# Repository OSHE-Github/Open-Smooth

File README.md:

# Open-Smooth
echo "# OPENSmooth" >> README.md
# Project Overview
OPENSmooth introduces an open-source 3D print post-processor that uses acetone vapor and heat to smooth filament layer lines. The system integrates electronic monitors to regulate exposure time and ensure safe operation, reducing risks associated with manual methods. By combining automated vapor control with real-time safety monitoring, the design provides a low-cost, accessible solution to improve the surface quality of 3D-printed parts.
# Bill of Materials

### Physical Construction
| Category | Item | Part Number | Source | Cost |
|----------|------|------------|--------|------|
| Physical Construction | PETG filament | - | Amazon | $15 (per spool) |
| Physical Construction | Enclosure bin | - | Amazon | $12 |
| Physical Construction | Plastic bottles | - | Amazon | $7 |
| Physical Construction | Fan grill | - | Amazon | $5 |
| Physical Construction | Epoxy | - | Amazon | $8 |

### Electronics
| Category | Item | Part Number | Source | Cost |
|----------|------|------------|--------|------|
| Electronics | Heater | - | Amazon | $35 |
| Electronics | Atomizers | - | Amazon | $23 |
| Electronics | Fans (x2) | - | Amazon | $18 |
| Electronics | E-stop | - | Amazon | $12 |
| Electronics | Touchscreen | - | Amazon | $16 |
| Electronics | Servo | - | Amazon | $19 |
| Electronics | IEC plug | - | Amazon | $8 |
| Electronics | IEC cable | - | Amazon | $6 |
| Electronics | RGB lights | - | Amazon | $13 |

### Circuitry
| Category | Item | Part Number | Source | Cost |
|----------|------|------------|--------|------|
| Circuitry | PCB | - | - | $10 |
| Circuitry | Arduino Mega | - | - | $30 |
| Circuitry | ATMEGA328 (x2) | - | DigiKey | $6 |
| Circuitry | Relays (x2) | - | Amazon | $14 |
| Circuitry | Buck converters | - | Amazon | $8 |
| Circuitry | 2N2222A Transistors (x20) | - | DigiKey | $1 |
| Circuitry | Thermistor | - | - | $8 |
| Circuitry | Acetone sensor | - | - | $8 |
| Circuitry | 12V power supply | - | Amazon | $10 |

### Consumables
| Category | Item | Part Number | Source | Cost |
|----------|------|------------|--------|------|
| Consumables | Acetone | - | Amazon | $10 |
| Consumables | Carbon pellets | - | Amazon | $12 |

---

## Tools Used

### Testing and Planning
| Category | Item | Part Number | Source | Cost |
|----------|------|------------|--------|------|
| Testing and Planning | Breadboard | ZYJ-102 | Adafruit | $5.95 |
| Testing and Planning | Multimeter | Fluke 179 | Fluke | $479.99 |
| Testing and Planning | Oscilloscope | MSO6012A | Test Equity | $2955.00 |

### Assembly
| Category | Item | Part Number | Source | Cost |
|----------|------|------------|--------|------|
| Assembly | Solder Iron | FX-888D | Hakko | $121.47 |
| Assembly | Dremel | - | Milwaukee | - |
| Assembly | Drill | - | Milwaukee | - |

### Programming
| Category | Item | Part Number | Source | Cost |
|----------|------|------------|--------|------|
| Programming | Arduino IDE | Arduino IDE 2.3.2 | Arduino | $0 |

# Assembly Overview
### 1. Print All Components
- 3D print all required parts using PETG filament
- Base components (13 parts)
- Filter components (9 parts)
- Rotating table components (4 parts) + servo housing (1 part)
- Recommended to have ~2kg of filament available
- Use supports only where necessary (mainly the table)

### 2. Assemble the Base
- Fit all base components together using the dovetail joints
- Ensure correct orientation (parts only fit one way)
- Press-fit assembly should hold the structure together
- Apply epoxy if additional strength is needed

### 3. Prepare and Assemble the Lid
- Cut and drill openings for:
  - Heater (rear-center)
  - Filter (top-center)
- Mount heater:
  - Cut a circular hole for the heater body
  - Drill mounting holes
  - Install the gasket and secure the heater
- Mount filter:
  - Cut a square intake hole
  - Drill mounting holes (M3)
- Install a limit switch at the bottom edge of the lid to detect the open/closed state

### 4. Assemble and Install the Filter
- Assemble the main filter housing using M3 screws
- Install a 60 mm fan and secure it with M4 screws
- Prepare pellet drawer:
  - Epoxy if printed in two parts
  - Fill with carbon pellets
- Insert pellet drawer and secure with clips and screws
- Cut mounting holes and vent in enclosure
- Attach filter and gasket to enclosure

### 5. Install the Rotating Table System
- Mount the servo into the servo housing
- Route wires through housing cutouts
- Install housing into base (center cutout)
- Attach the spur gear to the servo shaft
- Install the table spacer and the rotating table
- Snap the fan grille into place

### 6. Assemble Atomizers
- Assemble each atomizer:
  - Insert wick into atomizer
  - Secure wick using trimmed nail or pin
- Extend wiring to reach the control PCB
- Repeat for all atomizers
- Fill with acetone and place into holders

### 7. Final Assembly & Integration
- Ensure all mechanical components are secured
- Verify moving parts (table rotation, fan clearance)
- Confirm proper placement of heater, filter, and sensors
- Connect electronics (fans, heater, atomizers, sensors, etc.)
- Perform a system check before operation

### 8. Final Checks
- Verify all fasteners are tight
- Ensure no air leaks around the filter and heater
- Confirm limit switch functionality
- Test electrical connections safely

**Note:**  
Epoxy is optional in most areas but recommended for long-term durability.

# Future Improvements
### Enclosure Stability and Sealing Capability
The enclosure currently uses duct tape to keep a seal with the lid. This works well, but it could be improved. Adding a lid locking mechanism with a layered rubber seal at the base would prevent the lid from unintentionally opening as well as provide a better seal.

### Atomizer bottles
The atomizer bottles we used for this project are made of PET plastic. PET plastic is susceptible to acetone over long periods of time, causing the bottles to likely leak. In our testing, the bottles showed minimal wear, but this doesn't mean they are 100% safe. Bottles made of PP or HDPE plastic would be much better suited for this application.

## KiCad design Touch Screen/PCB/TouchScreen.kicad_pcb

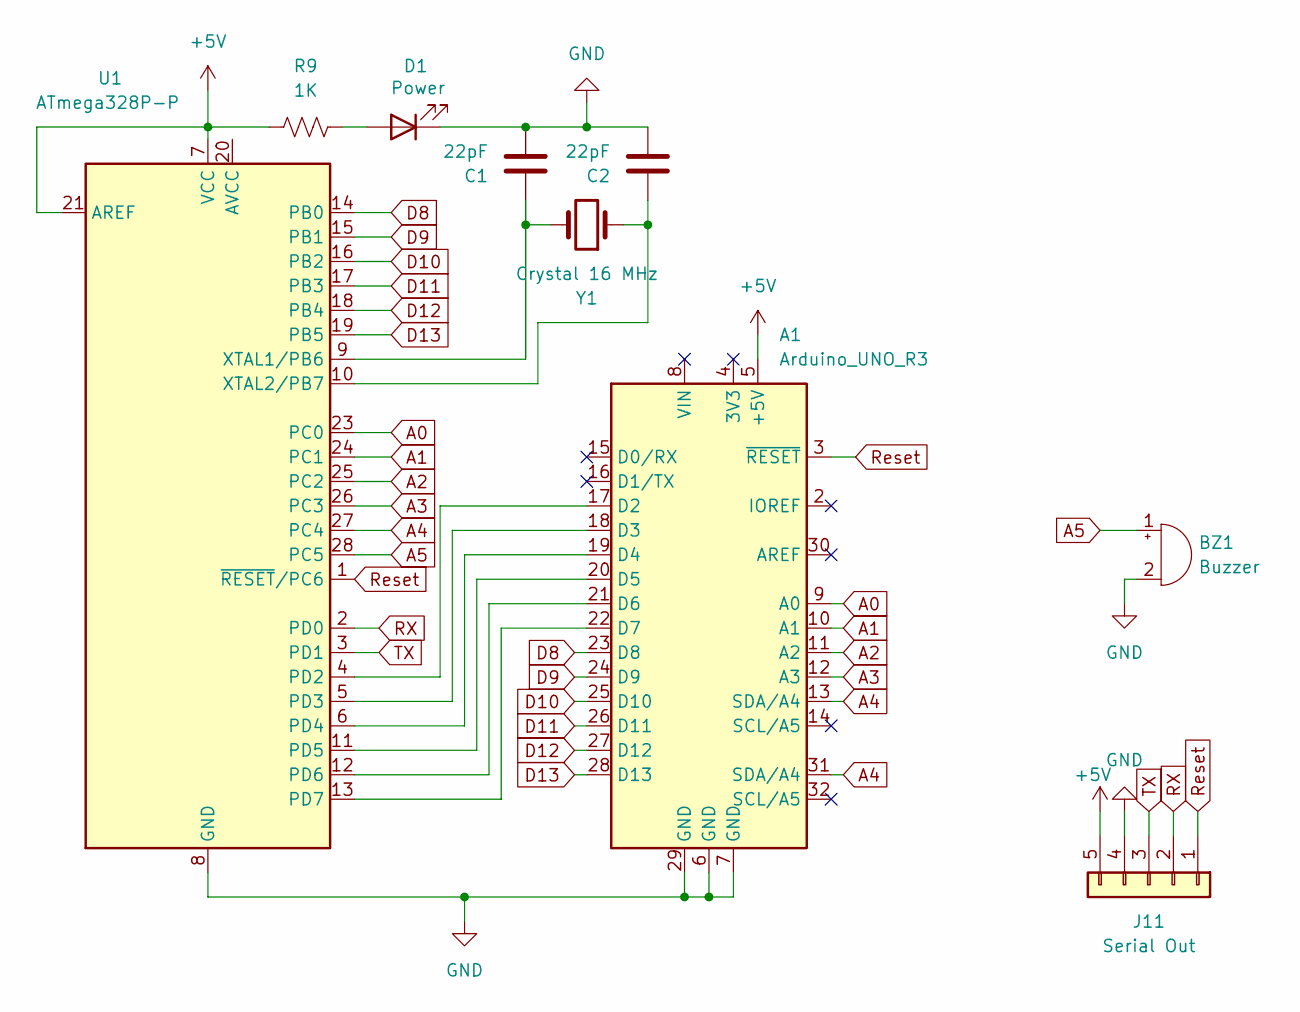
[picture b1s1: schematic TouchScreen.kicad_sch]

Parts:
A1: Arduino_UNO_R3
BZ1: Buzzer; Buzzer_12x9.5RM7.6
C1, C2: 22pF; C_Disc_D3.0mm_W1.6mm_P2.50mm
D1: Power; LED_D5.0mm
J11: Serial Out; JST_XH_B5B-XH-A_1x05_P2.50mm_Vertical
R9: 1K; R_Axial_DIN0309_L9.0mm_D3.2mm_P12.70mm_Horizontal
U1: ATmega328P-P; DIP-28_W7.62mm
Y1: Crystal 16 MHz; Crystal_HC49-4H_Vertical

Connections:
+5V: A1.5 (+5V), J11.5, R9.2, U1.7 (VCC), U1.21 (AREF)
A0: A1.9 (A0), U1.23 (PC0)
A1: A1.10 (A1), U1.24 (PC1)
A2: A1.11 (A2), U1.25 (PC2)
A3: A1.12 (A3), U1.26 (PC3)
A4: A1.13 (SDA/A4), A1.31 (SDA/A4), U1.27 (PC4)
A5: BZ1.1 (+), U1.28 (PC5)
D8: A1.23 (D8), U1.14 (PB0)
D9: A1.24 (D9), U1.15 (PB1)
D10: A1.25 (D10), U1.16 (PB2)
D11: A1.26 (D11), U1.17 (PB3)
D12: A1.27 (D12), U1.18 (PB4)
D13: A1.28 (D13), U1.19 (PB5)
GND: A1.6 (GND), A1.7 (GND), A1.29 (GND), BZ1.2 (-), C1.2, C2.2, D1.1 (K), J11.4, U1.8 (GND), U1.22 (GND)
unnamed: A1.17 (D2), U1.4 (PD2)
unnamed: A1.18 (D3), U1.5 (PD3)
unnamed: A1.19 (D4), U1.6 (PD4)
unnamed: A1.20 (D5), U1.11 (PD5)
unnamed: A1.21 (D6), U1.12 (PD6)
unnamed: A1.22 (D7), U1.13 (PD7)
unnamed: D1.2 (A), R9.1
unnamed: C1.1, U1.9 (XTAL1/PB6), Y1.2
unnamed: C2.1, U1.10 (XTAL2/PB7), Y1.1
RX: J11.2, U1.2 (PD0)
Reset: A1.3 (~RESET), J11.1, U1.1 (~RESET/PC6)
TX: J11.3, U1.3 (PD1)

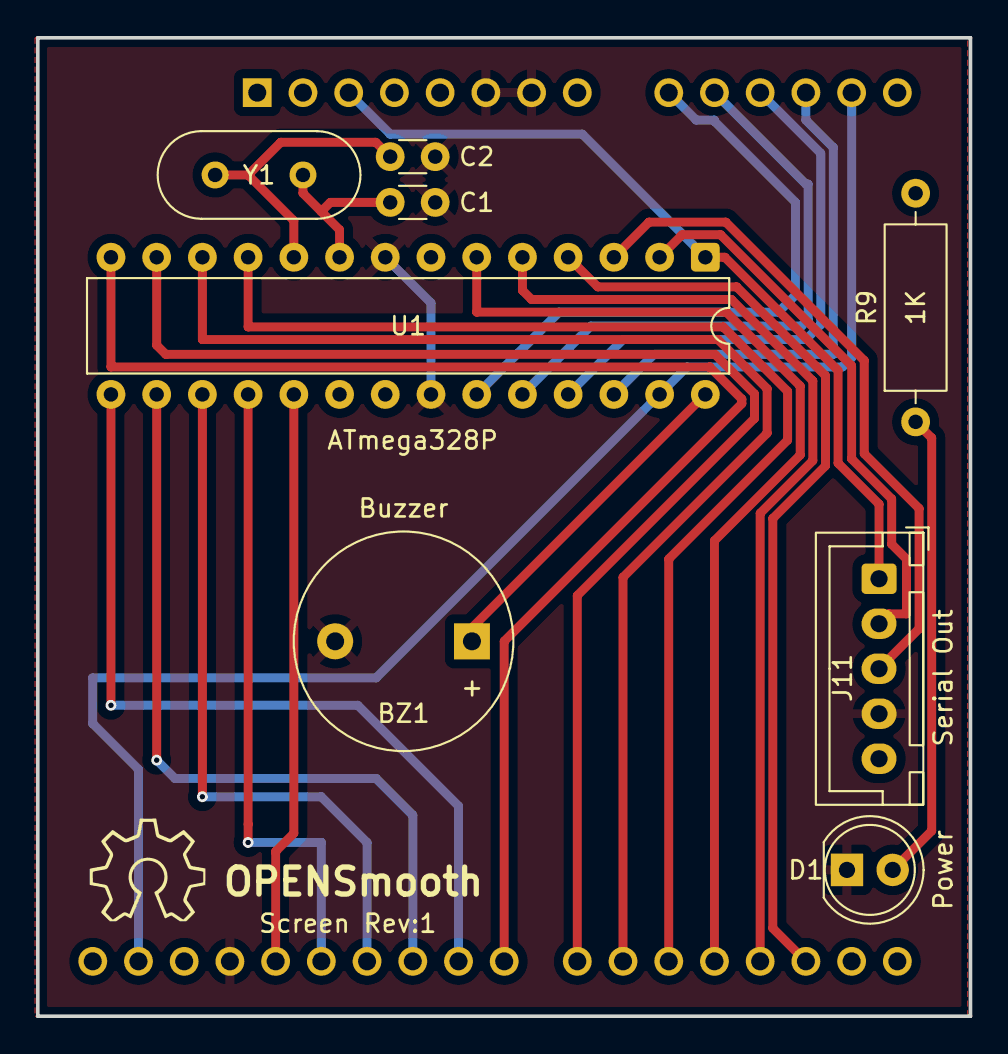
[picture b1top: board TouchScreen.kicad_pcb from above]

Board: 2 copper layers, 51.8 x 54.4 mm, 9 parts (0 on the bottom side), 26 nets.

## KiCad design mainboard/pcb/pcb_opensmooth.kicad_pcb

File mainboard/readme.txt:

Here is the code and kicad progect for the mainboard and pcb

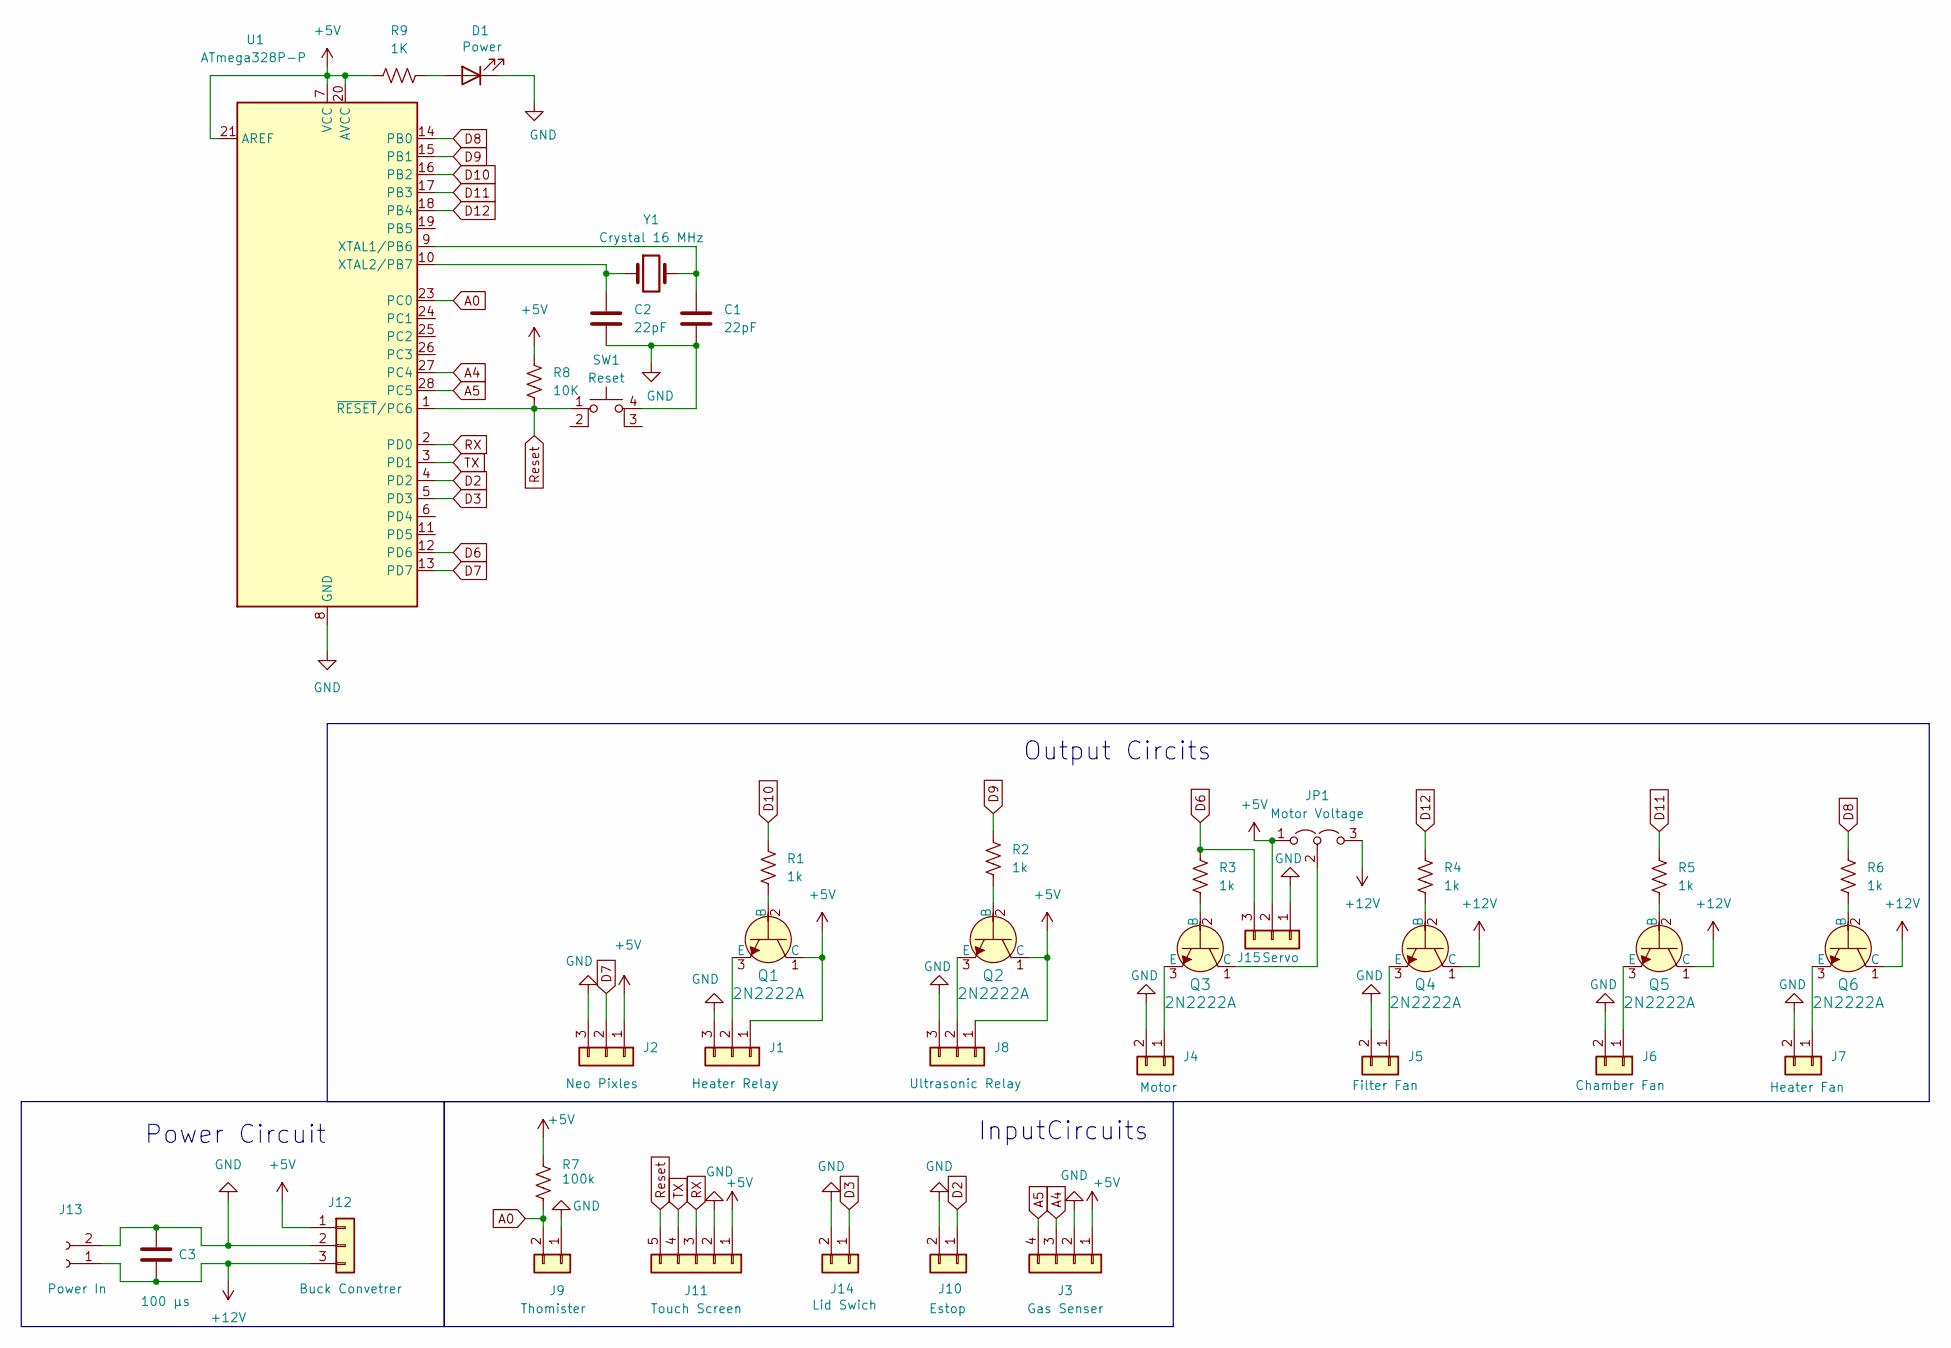
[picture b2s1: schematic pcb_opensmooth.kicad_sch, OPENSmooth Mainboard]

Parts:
C1, C2: 22pF; C_Disc_D3.0mm_W1.6mm_P2.50mm
C3: 100 μs; C_Radial_D6.3mm_H7.0mm_P2.50mm
D1: Power; LED_D5.0mm
J1: Heater Relay; JST_XH_B3B-XH-A_1x03_P2.50mm_Vertical
J2: Neo Pixles; JST_XH_B3B-XH-A_1x03_P2.50mm_Vertical
J3: Gas Senser; JST_XH_B4B-XH-A_1x04_P2.50mm_Vertical
J4: Motor; JST_XH_B2B-XH-A_1x02_P2.50mm_Vertical
J5: Filter Fan; JST_XH_B2B-XH-A_1x02_P2.50mm_Vertical
J6: Chamber Fan; JST_XH_B2B-XH-A_1x02_P2.50mm_Vertical
J7: Heater Fan; JST_XH_B2B-XH-A_1x02_P2.50mm_Vertical
J8: Ultrasonic Relay; JST_XH_B3B-XH-A_1x03_P2.50mm_Vertical
J9: Thomister; JST_XH_B2B-XH-A_1x02_P2.50mm_Vertical
J10: Estop; JST_XH_B2B-XH-A_1x02_P2.50mm_Vertical
J11: Touch Screen; JST_XH_B5B-XH-A_1x05_P2.50mm_Vertical
J12: Buck Convetrer; JST_XH_B3B-XH-A_1x03_P2.50mm_Vertical
J13: Power In; 282837-2_TYC
J14: Lid Swich; JST_XH_B2B-XH-A_1x02_P2.50mm_Vertical
J15: Servo; PinHeader_1x03_P2.54mm_Vertical
JP1: Motor Voltage; PinHeader_1x03_P2.54mm_Vertical
Q1, Q2, Q3, Q4, Q5, Q6: 2N2222A; 2n2222; MPN 2N2222A; Digi-Key_PN 2N2222ACS-ND
R1, R2, R3, R4, R5, R6: 1k; R_Axial_DIN0309_L9.0mm_D3.2mm_P12.70mm_Horizontal
R7: 100k; R_Axial_DIN0309_L9.0mm_D3.2mm_P12.70mm_Horizontal
R8: 10K; R_Axial_DIN0309_L9.0mm_D3.2mm_P12.70mm_Horizontal
R9: 1K; R_Axial_DIN0309_L9.0mm_D3.2mm_P12.70mm_Horizontal
SW1: Reset; Switch_Tactile_THT_6x6mm
U1: ATmega328P-P; DIP-28_W7.62mm
Y1: Crystal 16 MHz; Crystal_HC49-4H_Vertical

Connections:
+5V: J1.1, J2.1, J3.1, J8.1, J11.1, J12.1, J15.2, JP1.1 (A), Q1.1 (C), Q2.1 (C), R7.2, R8.2, R9.2, U1.7 (VCC), U1.20 (AVCC), U1.21 (AREF)
+12V: C3.2, J12.3, J13.1, JP1.3 (B), Q4.1 (C), Q5.1 (C), Q6.1 (C)
A0: J9.2, R7.1, U1.23 (PC0)
A4: J3.3, U1.27 (PC4)
A5: J3.4, U1.28 (PC5)
D2: J10.1, U1.4 (PD2)
D3: J14.1, U1.5 (PD3)
D6: J15.3, R3.2, U1.12 (PD6)
D7: J2.2, U1.13 (PD7)
D8: R6.2, U1.14 (PB0)
D9: R2.2, U1.15 (PB1)
D10: R1.2, U1.16 (PB2)
D11: R5.2, U1.17 (PB3)
D12: R4.2, U1.18 (PB4)
GND: C1.2, C2.2, C3.1, D1.1 (K), J1.3, J2.3, J3.2, J4.2, J5.2, J6.2, J7.2, J8.3, J9.1, J10.2, J11.2, J12.2, J13.2, J14.2, J15.1, SW1.4 (A), U1.8 (GND), U1.22 (GND)
unnamed: D1.2 (A), R9.1
unnamed: J1.2, Q1.3 (E)
unnamed: J4.1, Q3.3 (E)
unnamed: J5.1, Q4.3 (E)
unnamed: J6.1, Q5.3 (E)
unnamed: J7.1, Q6.3 (E)
unnamed: J8.2, Q2.3 (E)
unnamed: JP1.2 (C), Q3.1 (C)
unnamed: Q1.2 (B), R1.1
unnamed: Q2.2 (B), R2.1
unnamed: Q3.2 (B), R3.1
unnamed: Q4.2 (B), R4.1
unnamed: Q5.2 (B), R5.1
unnamed: Q6.2 (B), R6.1
unnamed: C1.1, U1.9 (XTAL1/PB6), Y1.2
unnamed: C2.1, U1.10 (XTAL2/PB7), Y1.1
RX: J11.3, U1.2 (PD0)
Reset: J11.5, R8.1, SW1.1, U1.1 (~RESET/PC6)
TX: J11.4, U1.3 (PD1)

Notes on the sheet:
InputCircuits
Output Circits
Power Circuit

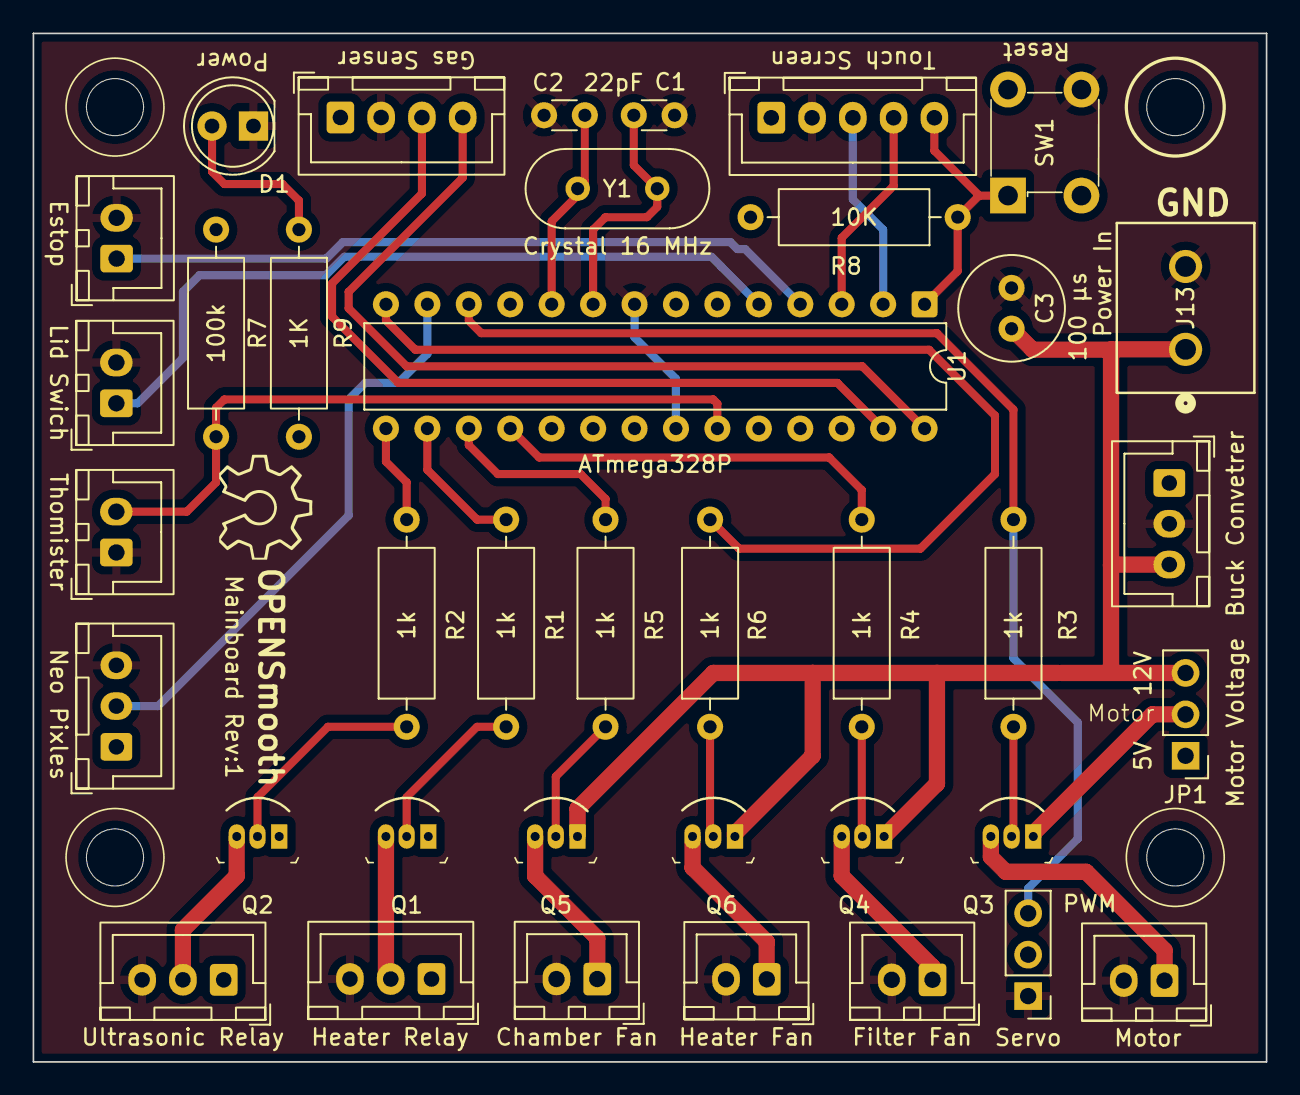
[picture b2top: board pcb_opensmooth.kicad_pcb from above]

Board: 2 copper layers, 75.6 x 63.0 mm, 38 parts (0 on the bottom side), 34 nets.

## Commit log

2026-02-08 Create code folder
2026-02-08 Create temp
2026-02-08 uploaded mainboard code
2026-02-08 uploaded mainboard pcb
